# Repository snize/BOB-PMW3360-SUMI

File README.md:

# PMW3360 breakout board - SUMI（墨）

ブレイクアウトボード自体はBoothから購入もできます https://bulblub.booth.pm/items/6164153

## 特徴

PMW3360用のコンパクトで低コストなブレイクアウトボードです。[PMW3610 breakout board \- SEIBOKU（青墨）](https://github.com/snize/BOB-PMW3610-SEIBOKU)と同様の設計思想で設計され、自作キーボードや自作トラックボールの試作や流用・組み込みを意識しています。

- 3.3Vのみで動作に限定することで部品点数を削減し低コスト・コンパクト化
- 手はんだでの実装を前提とし手はんだ用のパッドサイズと間隔を採用
- 平面的には基板の中心とOptical Centerが一致するように配置
- 立体的にはレンズ部の厚みは約3.4mm(PMW3610は約4.0mm)で若干の違いあり

## 寸法図/Dimensions

## 回路図/Schematic

## KiCanvasで見る

https://kicanvas.org/?github=https://github.com/snize/BOB-PMW3360-SUMI

## 部品表/BOM

| Reference | Value          | Qty  |
| --------- | -------------- | ---- |
| C1, C4    | 0.1uF          | 2    |
| C2        | 1uF            | 1    |
| C3        | 4.7uF/10V      | 1    |
| R1, R3    | 10k            | 2    |
| R2        | 39R            | 1    |
| U1        | TLV70019DDCR   | 1    |
| U2        | PMW3360DM-T2QU | 1    |

## 使用フォント/Font

本プロジェクトでは、**Departure Mono** フォントを使用しています。[rektdeckard/departure-mono](https://github.com/rektdeckard/departure-mono)

## ライセンス/License

This project is licensed under the CERN OHL-P v2.
You may use, distribute, and modify this design under the terms of the CERN OHL-P v2.
Original design by snize.

### 本プロジェクトを利用する場合について

- 著作権表示とライセンスの表示を残してください
- issueなどで利用した旨を報告していただけると作者が喜びます
  - 作例にバックリンクさせていただきます

## 本プロジェクトを利用した作例

DiscussionsやSNSでお知らせください！

- [HtCt44](https://github.com/snize/BOB-PMW3360-SUMI/discussions/5) by [sasadango-Jpn](https://github.com/sasadango-Jpn)
- [ortho47t](https://github.com/snize/BOB-PMW3360-SUMI/discussions/4) by [たかまる](https://x.com/Takamaru_FPV)
- [SouthernCrossTB（後付けトラックボール）](https://github.com/snize/BOB-PMW3360-SUMI/discussions/2) by [snize](https://x.com/snize)
- [Re:Square](https://github.com/snize/BOB-PMW3360-SUMI/discussions/6) by [へびたわ](https://x.com/hebino_tawagoto)

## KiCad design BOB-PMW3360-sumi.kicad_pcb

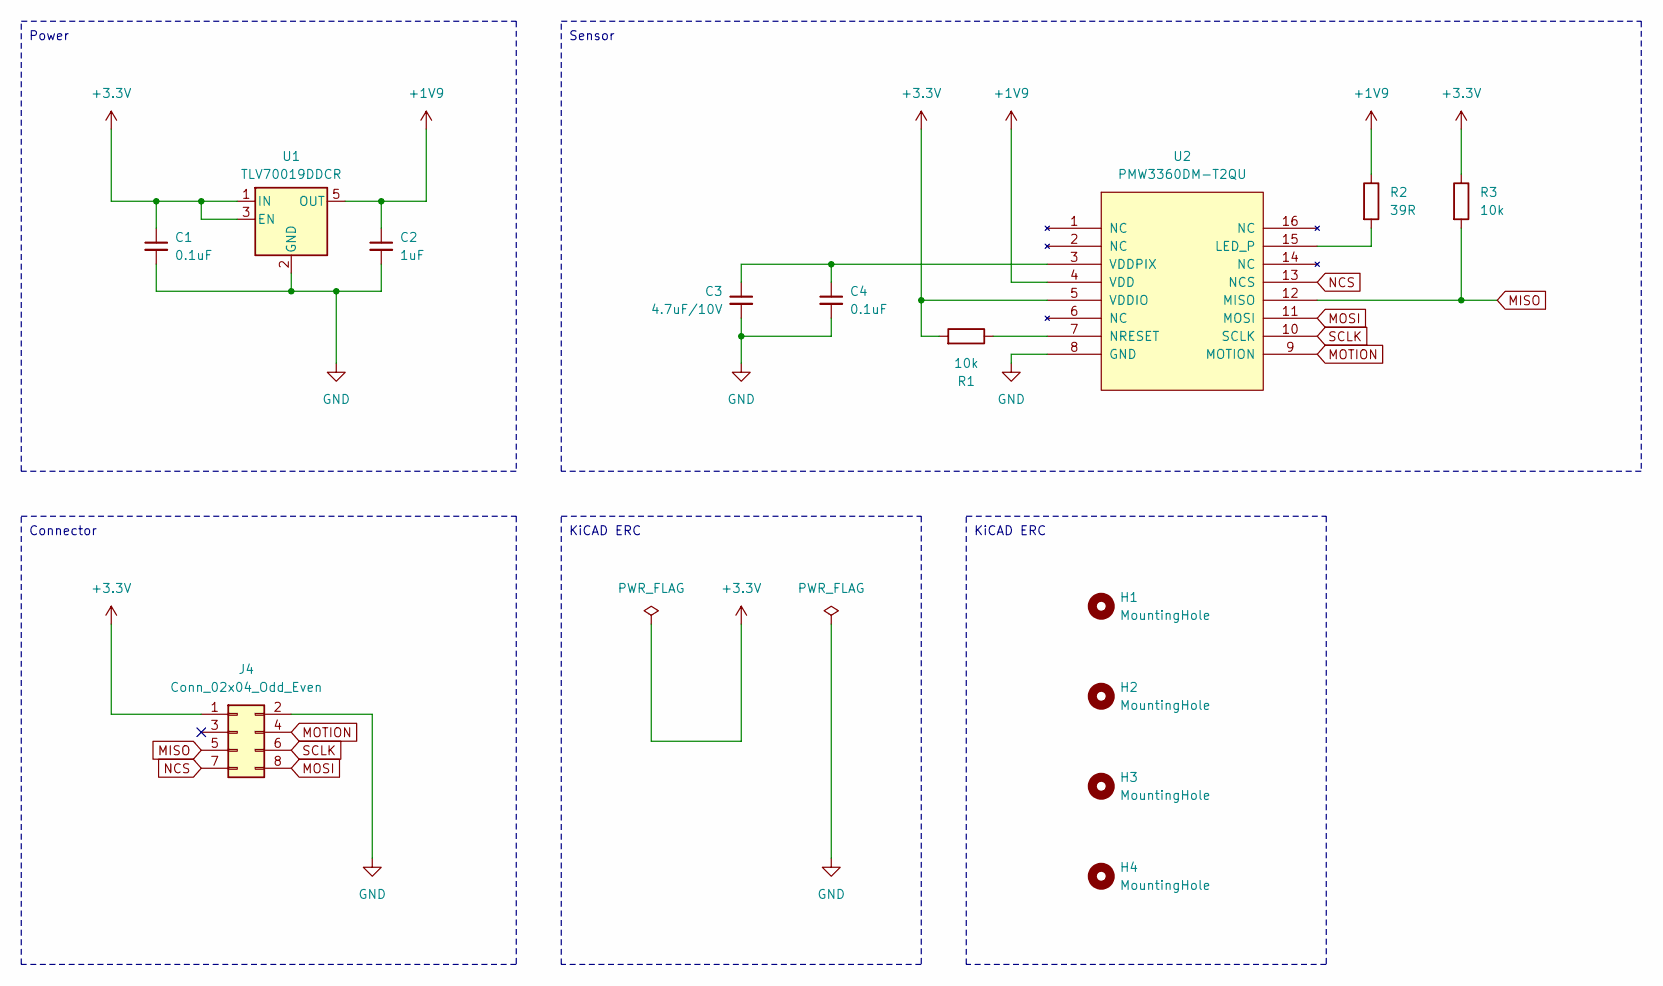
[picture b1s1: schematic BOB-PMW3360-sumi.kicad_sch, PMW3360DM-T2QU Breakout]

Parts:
C1, C4: 0.1uF; C_0805_2012Metric_Pad1.18x1.45mm_HandSolder
C2: 1uF; C_0805_2012Metric_Pad1.18x1.45mm_HandSolder
C3: 4.7uF/10V; C_0805_2012Metric_Pad1.18x1.45mm_HandSolder
H1, H2, H3, H4: MountingHole; MountingHole_2.2mm_M2_DIN965
J4: Conn_02x04_Odd_Even; PinHeader_2x04_P2.54mm_Vertical
R1, R3: 10k; R_0805_2012Metric_Pad1.20x1.40mm_HandSolder
R2: 39R; R_0805_2012Metric_Pad1.20x1.40mm_HandSolder
U1: TLV70019DDCR; SOT-23-5_HandSoldering
U2: PMW3360DM-T2QU

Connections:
+1V9: C2.1, R2.1, U1.5 (OUT), U2.4 (VDD)
+3.3V: C1.1, J4.1, R1.2, R3.1, U1.1 (IN), U1.3 (EN), U2.5 (VDDIO)
GND: C1.2, C2.2, C3.2, C4.2, J4.2, U1.2 (GND), U2.8 (GND)
MISO: J4.5, R3.2, U2.12 (MISO)
MOSI: J4.8, U2.11 (MOSI)
MOTION: J4.4, U2.9 (MOTION)
NCS: J4.7, U2.13 (NCS)
unnamed: R2.2, U2.15 (LED_P)
unnamed: R1.1, U2.7 (NRESET)
unnamed: C3.1, C4.1, U2.3 (VDDPIX)
SCLK: J4.6, U2.10 (SCLK)

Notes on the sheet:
Sensor
Power
KiCAD ERC
Connector

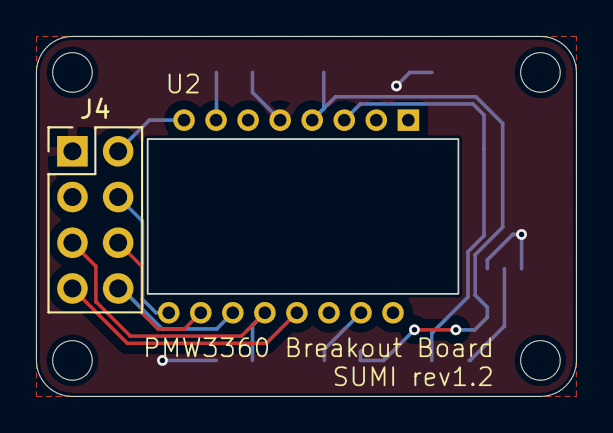
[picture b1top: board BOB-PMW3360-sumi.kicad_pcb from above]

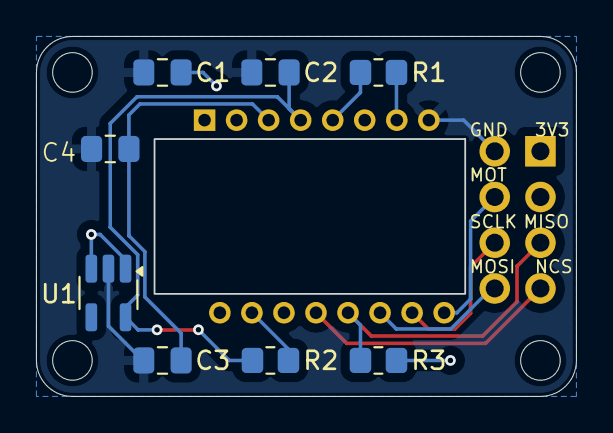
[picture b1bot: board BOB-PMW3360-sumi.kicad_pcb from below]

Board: 2 copper layers, 29.9 x 20.0 mm, 14 parts (8 on the bottom side), 11 nets.

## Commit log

2024-10-06 公開用最初のコミット
2024-10-06 寸法図を追加
2024-12-03 設計に変更なし。ドキュメント類整理
2024-12-03 README.mdの説明を更新
2025-01-31 Update README.md
    作例を追加
2025-05-04 シルクスクリーンとkicadのバージョンを8から9へ変更
2026-01-11 Add Re:Square discussion link to README
